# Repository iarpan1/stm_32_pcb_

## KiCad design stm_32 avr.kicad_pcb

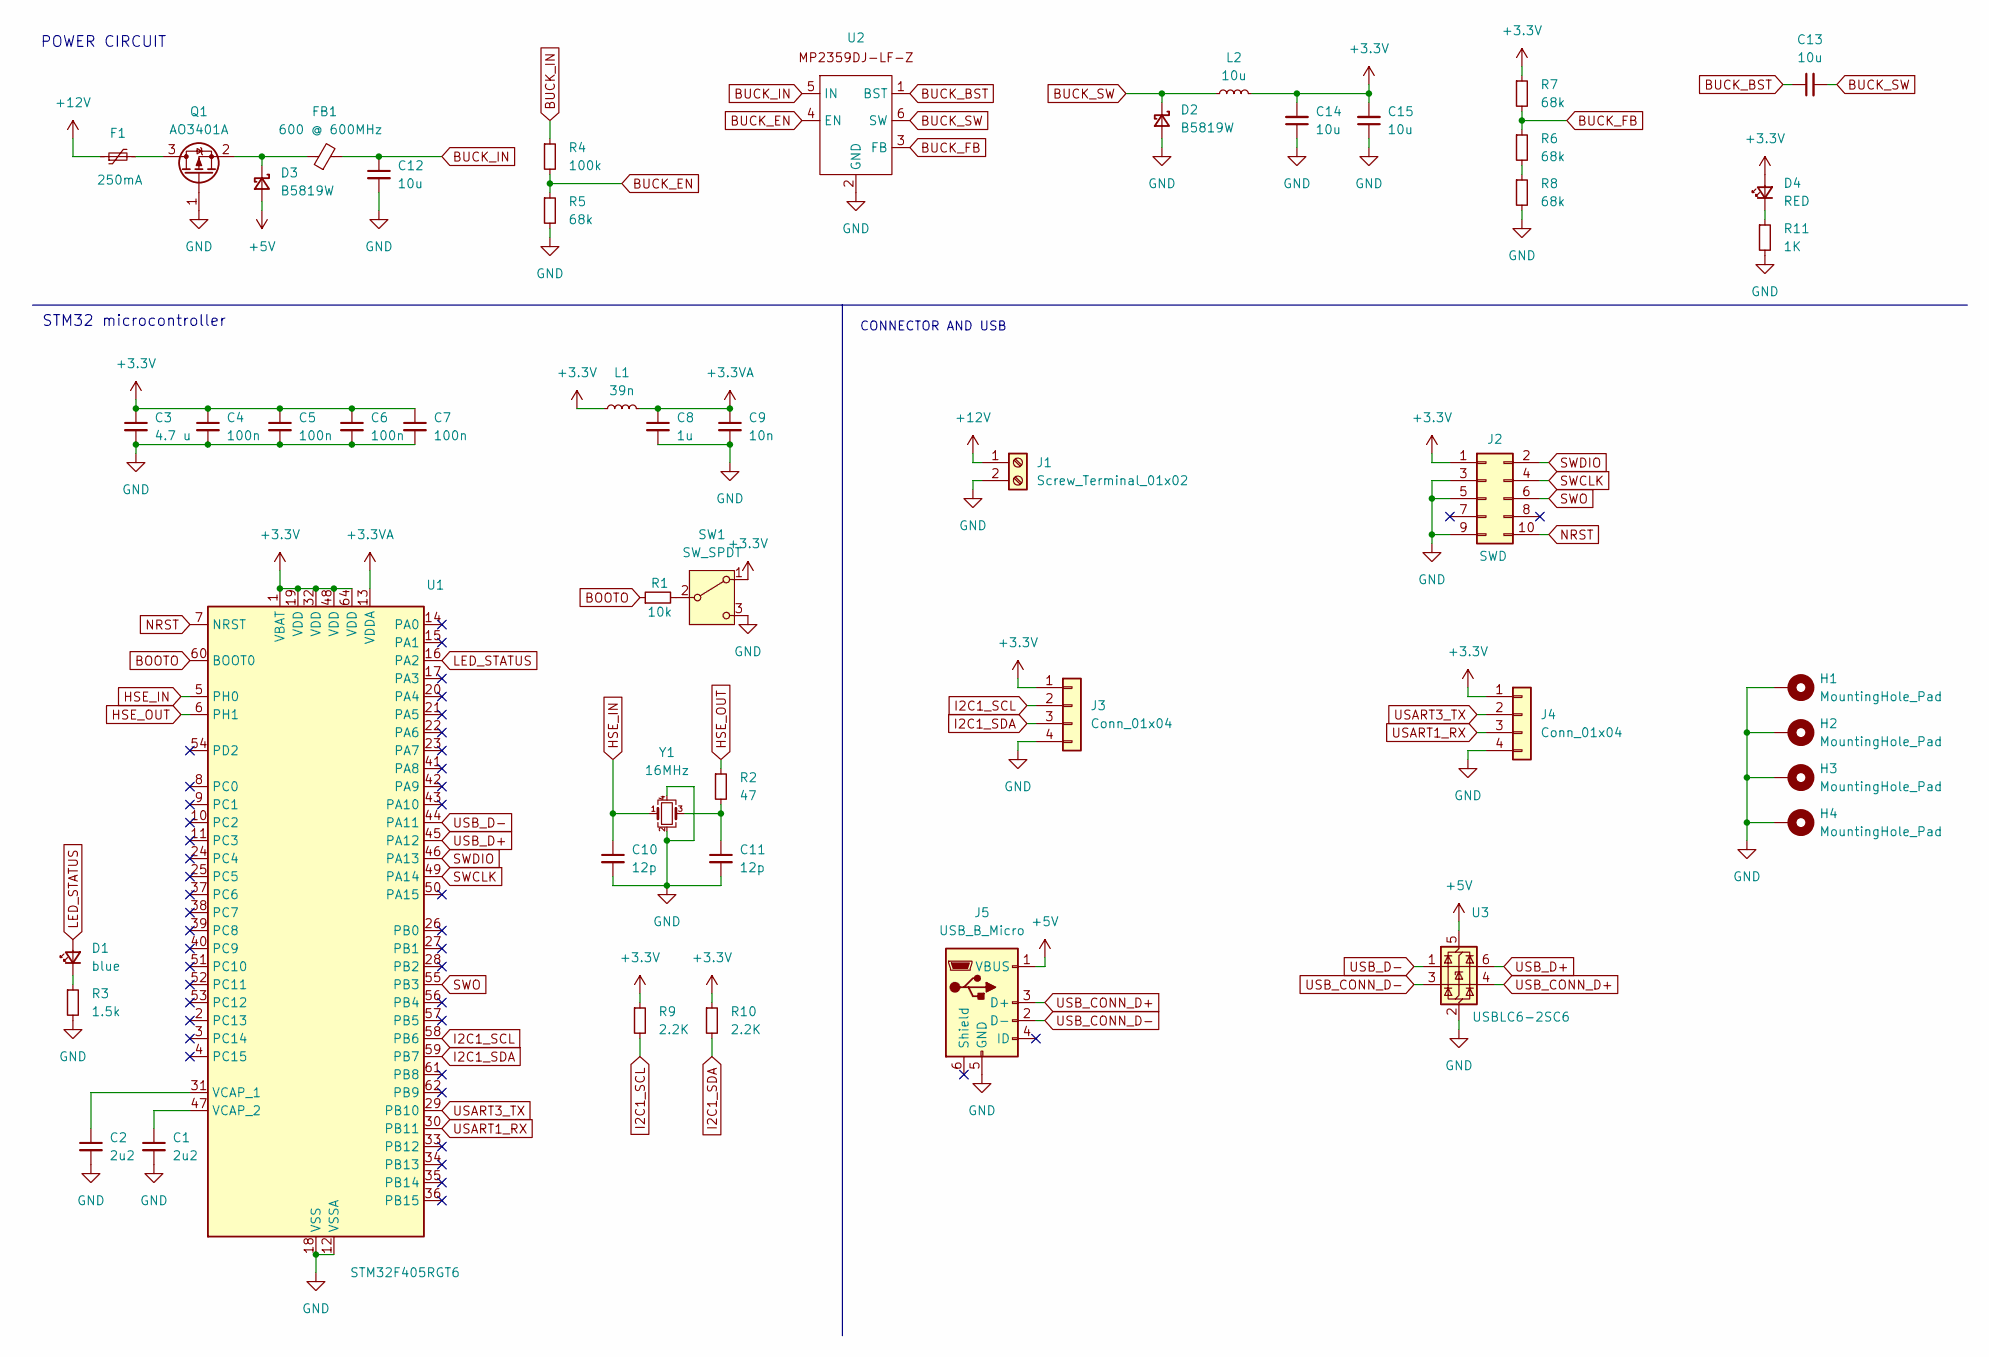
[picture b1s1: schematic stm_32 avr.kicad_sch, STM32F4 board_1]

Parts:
C1, C2: 2u2; C_0603_1608Metric
C3: 4.7 u; C_0402_1005Metric
C4: 100n; C_0402_1005Metric
C5, C6, C7: 100n; C_0504_1310Metric
C8: 1u; C_0402_1005Metric
C9: 10n; C_0402_1005Metric
C10, C11: 12p; C_0402_1005Metric
C12, C14, C15: 10u; C_1206_3216Metric
C13: 10u; C_0603_1608Metric
D1: blue; LED_0603_1608Metric
D2, D3: B5819W; D_SOD-123
D4: RED; LED_0603_1608Metric
F1: 250mA; Fuse_1206_3216Metric
FB1: 600 @ 600MHz; L_0805_2012Metric
H1, H2, H3, H4: MountingHole_Pad; MountingHole_4.3mm_M4_Pad_Via
J1: Screw_Terminal_01x02; TerminalBlock_Phoenix_PT-1,5-2-3.5-H_1x02_P3.50mm_Horizontal
J2: SWD; PinSocket_2x05_P1.27mm_Vertical_SMD
J3, J4: Conn_01x04; Molex_PicoBlade_53048-0410_1x04_P1.25mm_Horizontal
J5: USB_B_Micro; USB_Micro-B_Amphenol_10118193-0001LF_Horizontal
L1: 39n; L_Sunlord_MWSA0402S
L2: 10u; L_Sunlord_MWSA0518S
Q1: AO3401A; SOT-23
R1: 10k; R_0402_1005Metric
R2: 47; R_0402_1005Metric
R3: 1.5k; R_0612_1632Metric
R4: 100k; R_0612_1632Metric
R5, R6, R7, R8: 68k; R_0612_1632Metric
R9: 2.2K; R_0402_1005Metric
R10: 2.2K; R_0402_1005Metric_Pad0.72x0.64mm_HandSolder
R11: 1K; R_0612_1632Metric
SW1: SW_SPDT; SW_SPDT_PCM12
U1: STM32F405RGT6; LQFP-64_10x10mm_P0.5mm
U2: SOT-23-6
U3: USBLC6-2SC6; SOT-23-6
Y1: 16MHz; Crystal_SMD_3225-4Pin_3.2x2.5mm

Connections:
+3.3V: C3.1, C4.1, C5.1, C6.1, C7.1, C14.2, C15.2, D4.2 (A), J2.1, J3.1, J4.1, L1.1, L2.2, R7.1, R9.1, R10.1, SW1.1 (A), U1.1 (VBAT), U1.19 (VDD), U1.32 (VDD), U1.48 (VDD), U1.64 (VDD)
+3.3VA: C8.1, C9.1, L1.2, U1.13 (VDDA)
+5V: D3.2 (A), J5.1 (VBUS), U3.5 (VBUS)
+12V: F1.1, J1.1
BOOTO: R1.1, U1.60 (BOOT0)
BUCK_BST: C13.1, U2.1 (BST)
BUCK_EN: R4.2, R5.1, U2.4 (EN)
BUCK_FB: R6.1, R7.2, U2.3 (FB)
BUCK_IN: C12.1, FB1.2, R4.1, U2.5 (IN)
BUCK_SW: C13.2, D2.1 (K), L2.1, U2.6 (SW)
GND: C1.2, C2.2, C3.2, C4.2, C5.2, C6.2, C7.2, C8.2, C9.2, C10.2, C11.2, C12.2, C14.1, C15.1, D2.2 (A), H1.1, H2.1, H3.1, H4.1, J1.2, J2.3, J2.5, J2.9, J3.4, J4.4, J5.5 (GND), Q1.1 (G), R3.2, R5.2, R8.2, R11.2, SW1.3 (C), U1.12 (VSSA), U1.18 (VSS), U1.63 (VSS), U2.2 (GND), U3.2 (GND), Y1.2, Y1.4
HSE_IN: C10.1, U1.5 (PH0), Y1.1
HSE_OUT: R2.1, U1.6 (PH1)
I2C1_SCL: J3.2, R9.2, U1.58 (PB6)
I2C1_SDA: J3.3, R10.2, U1.59 (PB7)
LED_STATUS: D1.2 (A), U1.16 (PA2)
NRST: J2.10, U1.7 (NRST)
unnamed: C11.1, R2.2, Y1.3
unnamed: D1.1 (K), R3.1
unnamed: D3.1 (K), FB1.1, Q1.2 (S)
unnamed: D4.1 (K), R11.1
unnamed: F1.2, Q1.3 (D)
unnamed: R6.2, R8.1
unnamed: R1.2, SW1.2 (B)
unnamed: C2.1, U1.31 (VCAP_1)
unnamed: C1.1, U1.47 (VCAP_2)
SWCLK: J2.4, U1.49 (PA14)
SWDIO: J2.2, U1.46 (PA13)
SWO: J2.6, U1.55 (PB3)
USART1_RX: J4.3, U1.30 (PB11)
USART3_TX: J4.2, U1.29 (PB10)
USB_CONN_D+: J5.3 (D+), U3.4 (I/O2)
USB_CONN_D-: J5.2 (D-), U3.3 (I/O2)
USB_D+: U1.45 (PA12), U3.6 (I/O1)
USB_D-: U1.44 (PA11), U3.1 (I/O1)

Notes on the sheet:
STM32 microcontroller
CONNECTOR AND USB
POWER CIRCUIT

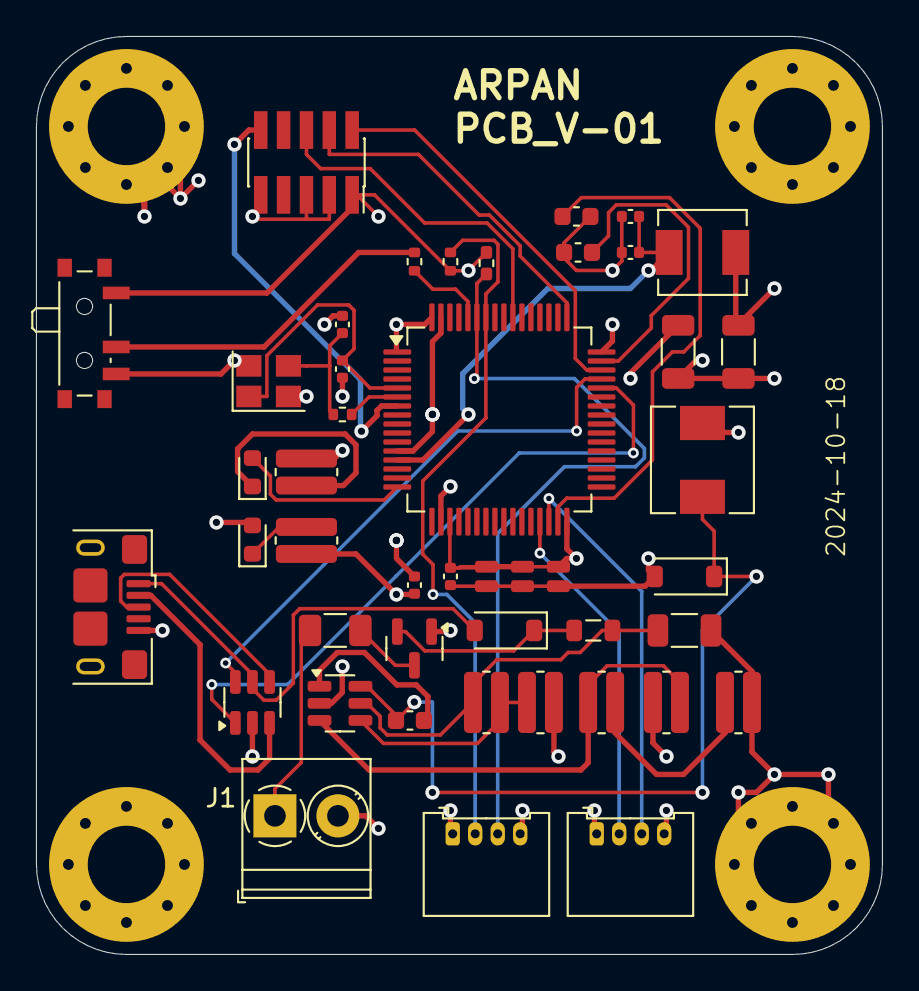
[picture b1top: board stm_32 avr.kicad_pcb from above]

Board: 4 copper layers, 47.0 x 51.0 mm, 49 parts (0 on the bottom side), 35 nets.

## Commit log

2024-10-19 Create usb_buck_converter
